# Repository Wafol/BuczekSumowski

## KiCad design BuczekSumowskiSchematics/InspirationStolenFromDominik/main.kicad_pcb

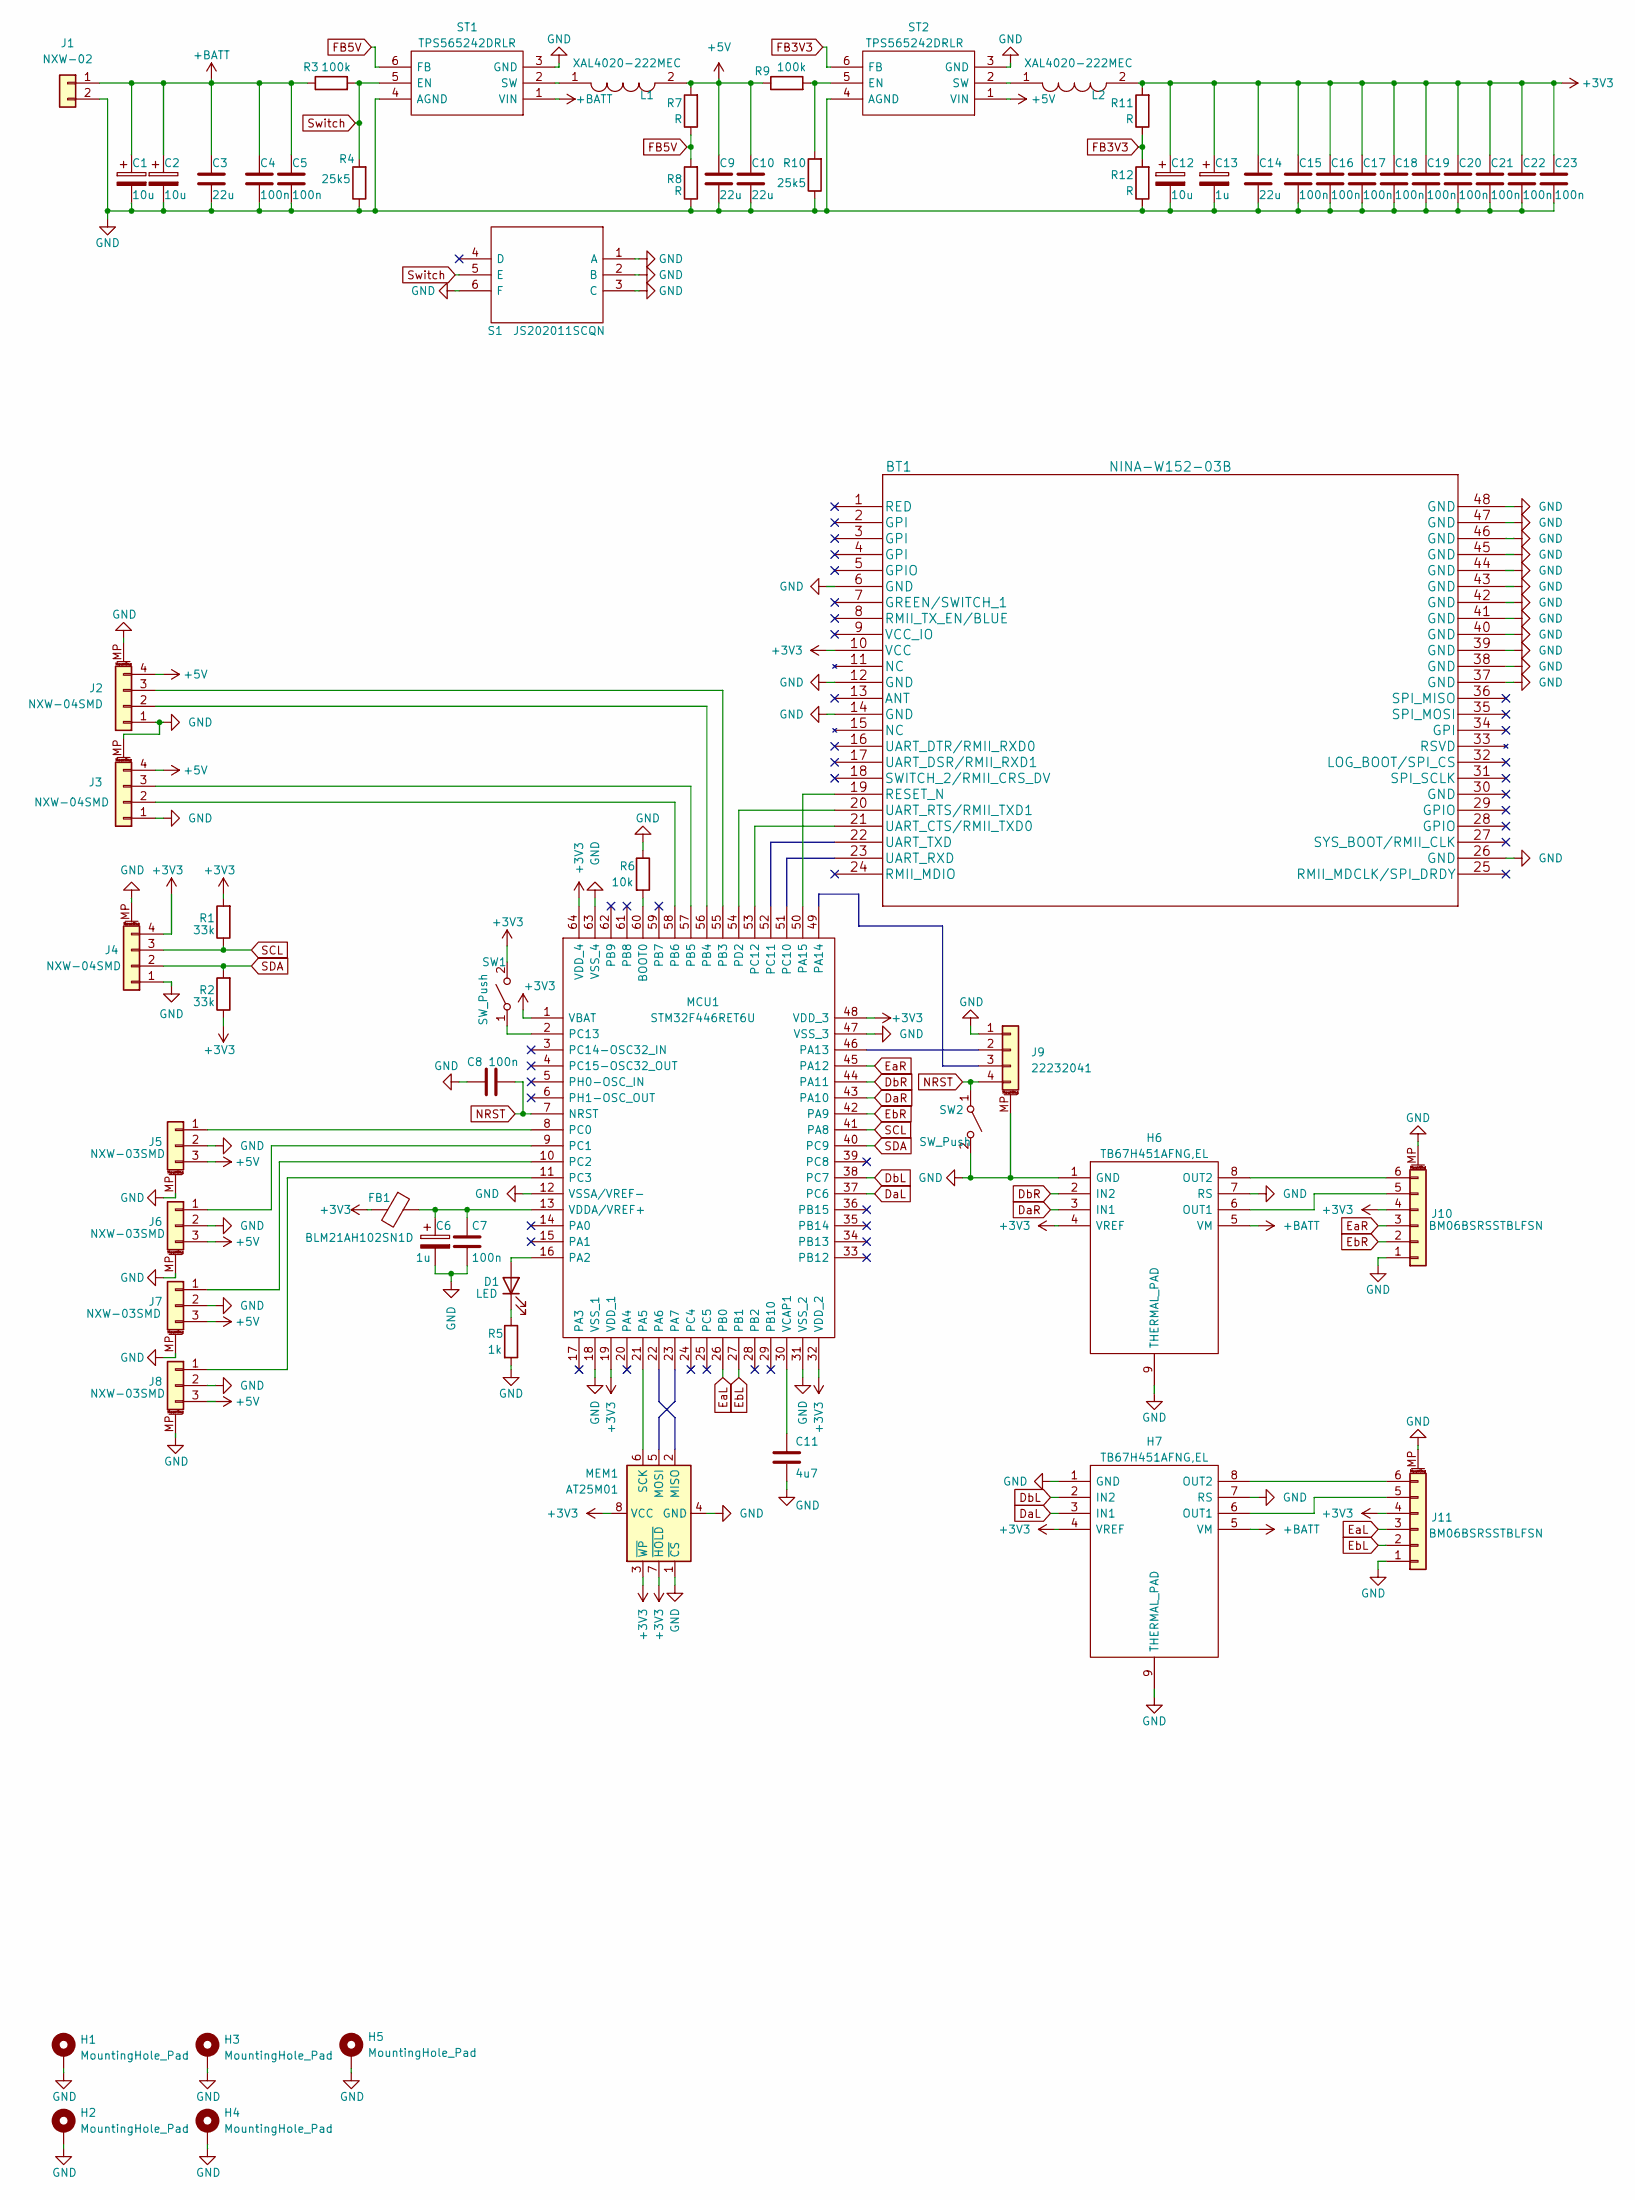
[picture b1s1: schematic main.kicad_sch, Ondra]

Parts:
BT1: NINA-W152-03B; nina-w152-03b
C1, C2, C12: 10u; CP_EIA-3216-18_Kemet-A_Pad1.58x1.35mm_HandSolder
C3, C9, C10, C14: 22u; C_0805_2012Metric_Pad1.18x1.45mm_HandSolder
C4, C5, C7, C8, C15, C16, C17, C18, C19, C20, C21, C22, C23: 100n; C_0805_2012Metric_Pad1.18x1.45mm_HandSolder
C6, C13: 1u; CP_EIA-3216-18_Kemet-A_Pad1.58x1.35mm_HandSolder
C11: 4u7; C_0805_2012Metric
D1: LED; LED_1206_3216Metric_Pad1.42x1.75mm_HandSolder
FB1: BLM21AH102SN1D; R_0805_2012Metric_Pad1.20x1.40mm_HandSolder
H1, H2, H3, H4, H5: MountingHole_Pad; MountingHole_3.2mm_M3_Pad_Via
H6, H7: TB67H451AFNG,EL; HSOP-8-1EP_3.9x4.9mm_P1.27mm_EP2.41x3.1mm_ThermalVias
J1: NXW-02; Molex_Micro-Latch_53253-0270_1x02_P2.00mm_Vertical
J2, J3, J4: NXW-04SMD; Molex_CLIK-Mate_502443-0470_1x04-1MP_P2.00mm_Vertical
J5, J6, J7, J8: NXW-03SMD; Molex_CLIK-Mate_502443-0370_1x03-1MP_P2.00mm_Vertical
J9: 22232041; Molex_KK-254_AE-6410-04A_1x04_P2.54mm_Vertical
J10, J11: BM06BSRSSTBLFSN; JST_SHL_SM06B-SHLS-TF_1x06-1MP_P1.00mm_Horizontal
L1, L2: XAL4020-222MEC; L_Coilcraft_XxL4040
MCU1: STM32F446RET6U; QFP50P1200X1200X160-64N
MEM1: AT25M01; SOIC-8_3.9x4.9mm_P1.27mm
R1, R2: 33k; R_0805_2012Metric_Pad1.20x1.40mm_HandSolder
R3, R9: 100k; R_0805_2012Metric_Pad1.20x1.40mm_HandSolder
R4, R10: 25k5; R_0805_2012Metric_Pad1.20x1.40mm_HandSolder
R5: 1k; R_0805_2012Metric_Pad1.20x1.40mm_HandSolder
R6: 10k; R_0805_2012Metric_Pad1.20x1.40mm_HandSolder
R7, R8, R11, R12: R; R_0805_2012Metric_Pad1.20x1.40mm_HandSolder
S1: JS202011SCQN; MSS6VTR
ST1, ST2: TPS565242DRLR; SOT-563
SW1, SW2: SW_Push; SW_Push_SPST_NO_Alps_SKRK

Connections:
+3V3: BT1.10 (VCC), C12.1, C13.1, C14.1, C15.1, C16.1, C17.1, C18.1, C19.1, C20.1, C21.1, C22.1, C23.1, FB1.2, H6.4 (VREF), H7.4 (VREF), J4.4, J10.4, J11.4, L2.2, MCU1.1 (VBAT), MCU1.19 (VDD_1), MCU1.32 (VDD_2), MCU1.48 (VDD_3), MCU1.64 (VDD_4), MEM1.3 (~WP), MEM1.7 (~HOLD), MEM1.8 (VCC), R1.2, R2.1, R11.2, SW1.2 (B)
+5V: C9.1, C10.1, J2.4, J3.4, J5.3, J6.3, J7.3, J8.3, L1.2, R7.2, R9.1, ST2.1 (VIN)
+BATT: C1.1, C2.1, C3.1, C4.1, C5.1, H6.5 (VM), H7.5 (VM), J1.1, R3.1, ST1.1 (VIN)
DaL: H7.3 (IN1), MCU1.37 (PC6)
DaR: H6.3 (IN1), MCU1.43 (PA10)
DbL: H7.2 (IN2), MCU1.38 (PC7)
DbR: H6.2 (IN2), MCU1.44 (PA11)
EaL: J11.3, MCU1.26 (PB0)
EaR: J10.3, MCU1.45 (PA12)
EbL: J11.2, MCU1.27 (PB1)
EbR: J10.2, MCU1.42 (PA9)
FB3V3: R11.1, R12.2, ST2.6 (FB)
FB5V: R7.1, R8.2, ST1.6 (FB)
GND: BT1.6 (GND), BT1.12 (GND), BT1.14 (GND), BT1.26 (GND), BT1.37 (GND), BT1.38 (GND), BT1.39 (GND), BT1.40 (GND), BT1.41 (GND), BT1.42 (GND), BT1.43 (GND), BT1.44 (GND), BT1.45 (GND), BT1.46 (GND), BT1.47 (GND), BT1.48 (GND), C1.2, C2.2, C3.2, C4.2, C5.2, C6.2, C7.2, C8.1, C9.2, C10.2, C11.2, C12.2, C13.2, C14.2, C15.2, C16.2, C17.2, C18.2, C19.2, C20.2, C21.2, C22.2, C23.2, H1.1, H2.1, H3.1, H4.1, H5.1, H6.1 (GND), H6.7 (RS), H6.9 (THERMAL_PAD), H7.1 (GND), H7.7 (RS), H7.9 (THERMAL_PAD), J1.2, J2.1, J2.MP (MountPin), J3.1, J3.MP (MountPin), J4.1, J4.MP (MountPin), J5.2, J5.MP (MountPin), J6.2, J6.MP (MountPin), J7.2, J7.MP (MountPin), J8.2, J8.MP (MountPin), J9.1, J9.MP (MountPin), J10.1, J10.MP (MountPin), J11.1, J11.MP (MountPin), MCU1.12 (VSSA/VREF-), MCU1.18 (VSS_1), MCU1.31 (VSS_2), MCU1.47 (VSS_3), MCU1.63 (VSS_4), MEM1.1 (~CS), MEM1.4 (GND), R4.1, R5.2, R6.1, R8.1, R10.1, R12.1, S1.1 (A), S1.2 (B), S1.3 (C), S1.6 (F), ST1.3 (GND), ST1.4 (AGND), ST2.3 (GND), ST2.4 (AGND), SW2.2 (B)
NRST: C8.2, J9.4, MCU1.7 (NRST), SW2.1 (A)
unnamed: BT1.19 (RESET_N), MCU1.50 (PA15)
unnamed: BT1.20 (UART_RTS/RMII_TXD1), MCU1.54 (PD2)
unnamed: BT1.21 (UART_CTS/RMII_TXD0), MCU1.53 (PC12)
unnamed: BT1.22 (UART_TXD), MCU1.52 (PC11)
unnamed: BT1.23 (UART_RXD), MCU1.51 (PC10)
unnamed: C6.1, C7.1, FB1.1, MCU1.13 (VDDA/VREF+)
unnamed: C11.1, MCU1.30 (VCAP1)
unnamed: D1.1 (K), R5.1
unnamed: D1.2 (A), MCU1.16 (PA2)
unnamed: H6.6 (OUT1), J10.5
unnamed: H6.8 (OUT2), J10.6
unnamed: H7.6 (OUT1), J11.5
unnamed: H7.8 (OUT2), J11.6
unnamed: J2.2, MCU1.56 (PB4)
unnamed: J2.3, MCU1.55 (PB3)
unnamed: J3.2, MCU1.58 (PB6)
unnamed: J3.3, MCU1.57 (PB5)
unnamed: J5.1, MCU1.8 (PC0)
unnamed: J6.1, MCU1.9 (PC1)
unnamed: J7.1, MCU1.10 (PC2)
unnamed: J8.1, MCU1.11 (PC3)
unnamed: J9.2, MCU1.46 (PA13)
unnamed: J9.3, MCU1.49 (PA14)
unnamed: L1.1, ST1.2 (SW)
unnamed: L2.1, ST2.2 (SW)
unnamed: MCU1.2 (PC13), SW1.1 (A)
unnamed: MCU1.21 (PA5), MEM1.6 (SCK)
unnamed: MCU1.22 (PA6), MEM1.2 (MISO)
unnamed: MCU1.23 (PA7), MEM1.5 (MOSI)
unnamed: MCU1.60 (BOOT0), R6.2
unnamed: R9.2, R10.2, ST2.5 (EN)
SCL: J4.3, MCU1.41 (PA8), R1.1
SDA: J4.2, MCU1.40 (PC9), R2.2
Switch: R3.2, R4.2, S1.5 (E), ST1.5 (EN)

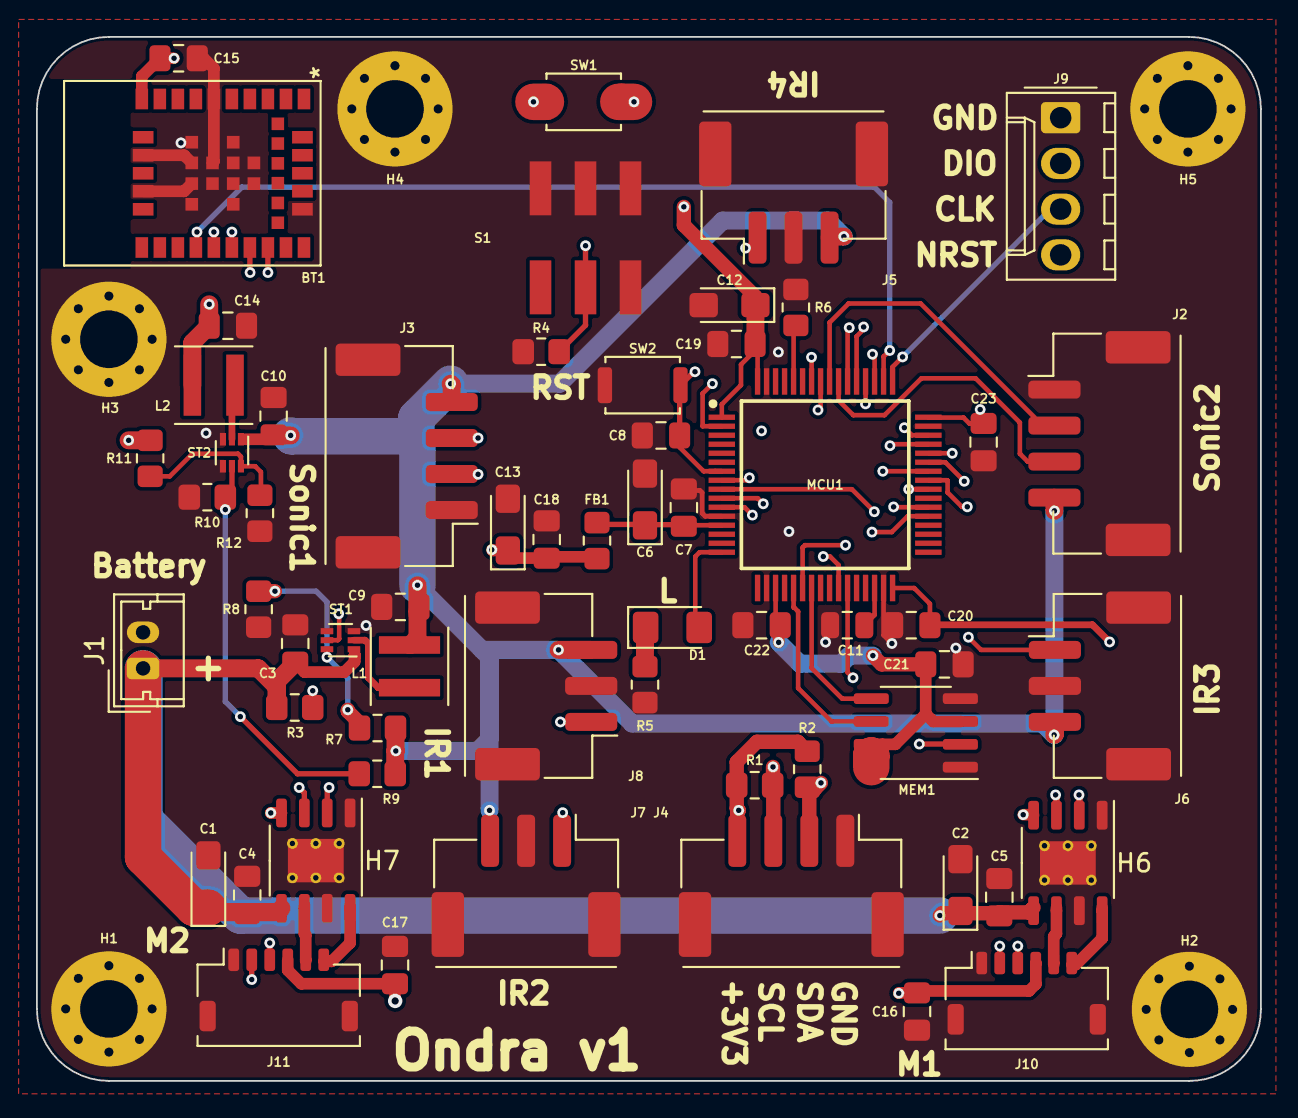
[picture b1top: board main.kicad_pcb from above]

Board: 4 copper layers, 68.0 x 58.0 mm, 65 parts (0 on the bottom side), 49 nets.

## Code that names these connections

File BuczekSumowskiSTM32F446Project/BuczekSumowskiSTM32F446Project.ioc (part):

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Mcu.Name=STM32F446R(C-E)Tx
Mcu.Package=LQFP64
Mcu.UserName=STM32F446RETx
PA11.Mode=Device_Only
PA11.Signal=USB_OTG_FS_DM
PA12.Mode=Device_Only
PA12.Signal=USB_OTG_FS_DP
PA13.Mode=Serial_Wire
PA13.Signal=SYS_JTMS-SWDIO
PA14.Mode=Serial_Wire
PA14.Signal=SYS_JTCK-SWCLK
PB4.Signal=S_TIM3_CH1
PB5.Signal=S_TIM3_CH2
PB6.Signal=S_TIM4_CH1
PB7.Signal=S_TIM4_CH2
PH0-OSC_IN.Mode=HSE-External-Oscillator
PH0-OSC_IN.Signal=RCC_OSC_IN
PH1-OSC_OUT.Mode=HSE-External-Oscillator
PH1-OSC_OUT.Signal=RCC_OSC_OUT
RCC.HSE_VALUE=16000000
board=custom

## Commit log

2023-05-03 fucking working laser sensor program
2023-05-03 schematic done
2023-05-09 Motors driving
2023-08-30 fresh start from new schematic
2023-08-30 basic stm32 connection (without source)
2023-08-30 schemtics progress
2023-08-31 schmetics updates
2023-09-01 schematic sensors added
2023-09-01 almost ready for check (maybe diff h-bridge?)
2023-09-01 better orginized
2024-03-02 partlist added
2024-03-04 basic components placed

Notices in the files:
parts and their libraries:
Copyright 2021 Accelerated Designs. All rights reserved.
